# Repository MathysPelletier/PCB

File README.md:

Circuits imprimé pour la carte mère et le ESP32. Logiciel utilisé : KiCad 8.0

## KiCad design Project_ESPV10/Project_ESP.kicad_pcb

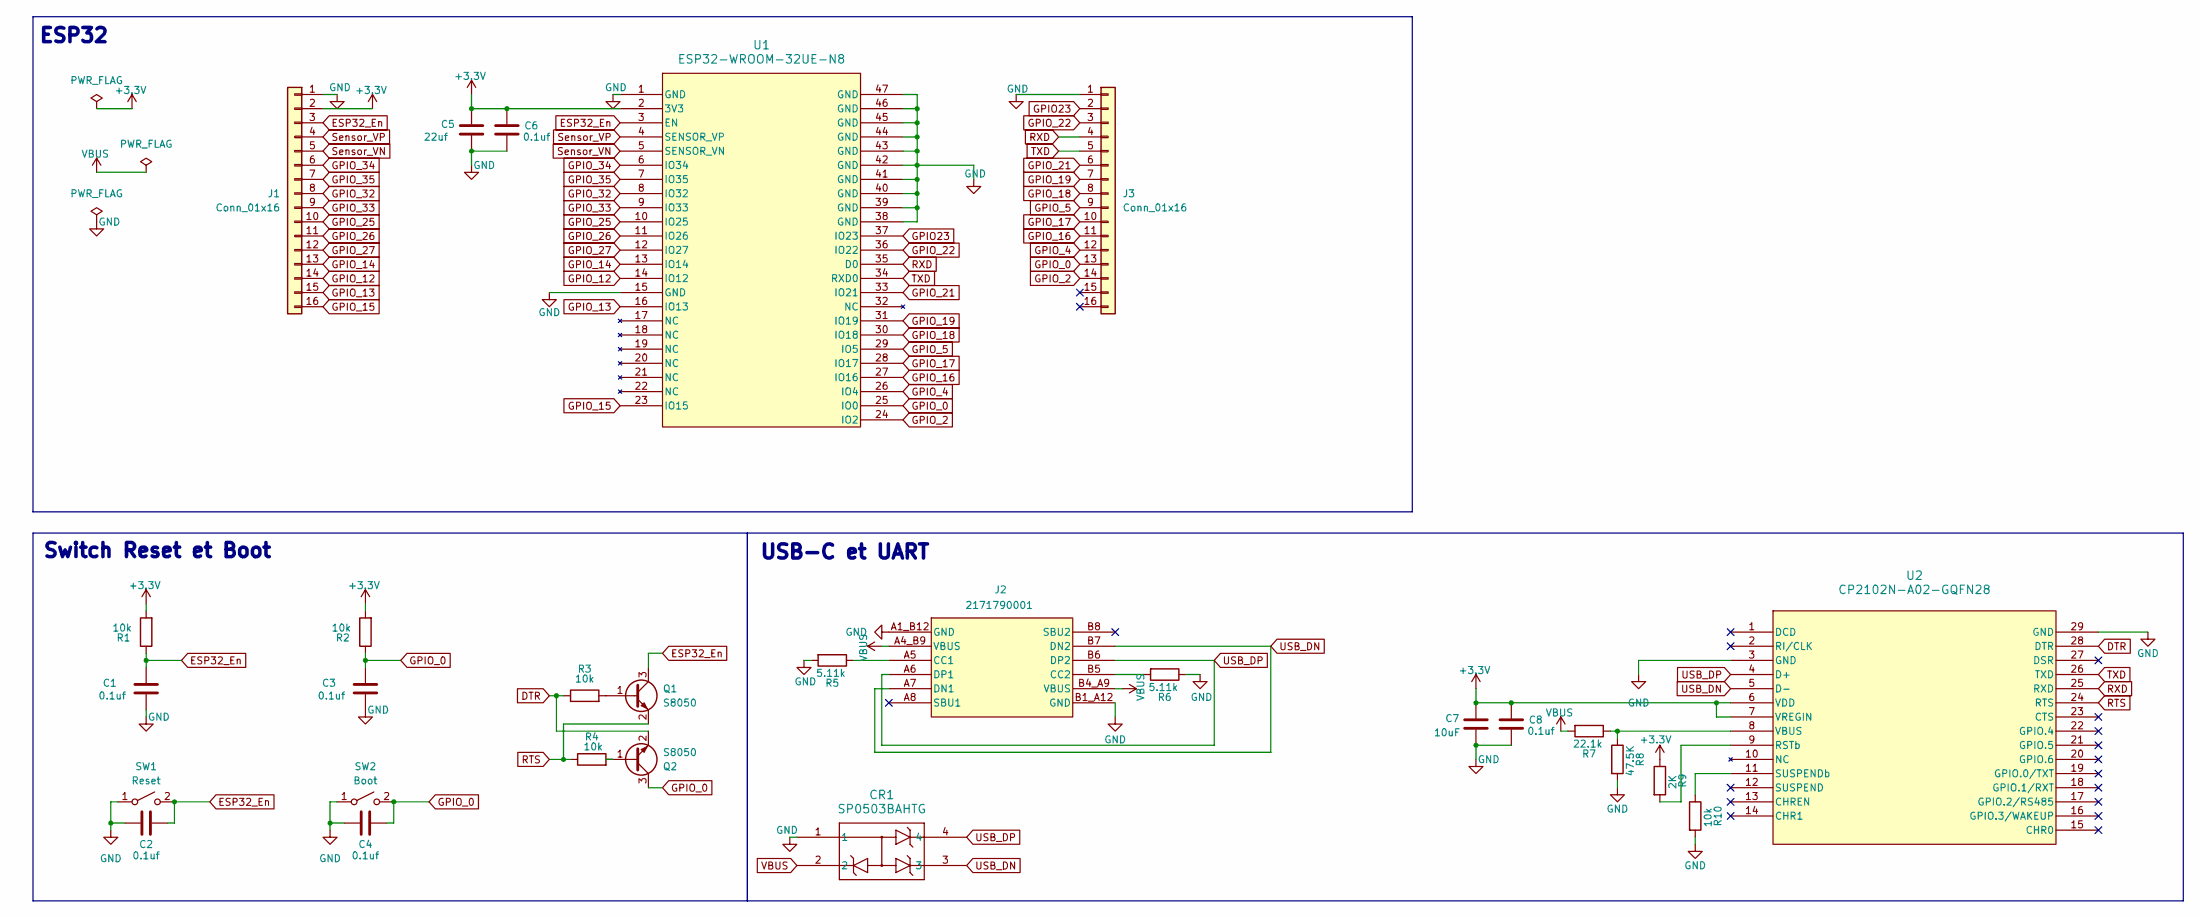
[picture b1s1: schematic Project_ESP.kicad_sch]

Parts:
C1, C2, C3, C4, C6, C8: 0.1uf; YAG_CC0603_YAG-M; part_number CC0603KRX7R8BB104
C5: 22uf; YAG_CC0603_YAG-M; part_number GRM188R61A226ME15D
C7: 10uF; YAG_CC0603_YAG-M; part_number JMK107ABJ106MA-T
CR1: SP0503BAHTG; TVS-SP05_LTF; part_number SP0503BAHTG
J1, J3: Conn_01x16; PinHeader_1x16_P2.54mm_Vertical
J2: 2171790001; GCT_USB4105-GF-A; PARTREV A1
Q1, Q2: S8050; TRAN_SS8050-G_CIP-M; part_number SS8050-G
R1, R2, R3, R4, R10: 10k; STA_RMCF0603_STP-M; part_number RMCF0603JT10K0
R5, R6: 5.11k; STA_RMCF0603_STP-M; part_number CRCW06035K11FKEAC
R7: 22.1k; STA_RMCF0603_STP-M; part_number RMCF0603FT22K1
R8: 47.5K; STA_RMCF0603_STP-M; part_number RMCF0603FT47K5
R9: 2K; STA_RMCF0603_STP-M; part_number ERJ-3EKF2001V
SW1: Reset; PTS636_SK; part_number PTS636 SK43 SMTR LFS
SW2: Boot; PTS636_SK; part_number PTS636 SK43 SMTR LFS
U1: ESP32-WROOM-32UE-N8; ESP32-WROOM-32UE_EXP; part_number ESP32-WROOM-32UE-N8
U2: CP2102N-A02-GQFN28; QFN28_5X5_SIL; part_number CP2102N-A02-GQFN28

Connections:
+3.3V: C5.2, C6.2, C7.2, C8.2, J1.2, R1.2, R2.2, R9.1, U1.2 (3V3), U2.6 (VDD), U2.7 (VREGIN)
DTR: Q2.2 (E), R3.1, U2.28 (DTR)
ESP32_En: C1.2, C2.2, J1.3, Q1.3 (C), R1.1, SW1.2 (B), U1.3 (EN)
GND: C1.1, C2.1, C3.1, C4.1, C5.1, C6.1, C7.1, C8.1, CR1.1, J1.1, J2.A1_B12 (GND), J2.B1_A12 (GND), J3.1, R5.2, R6.1, R8.2, R10.2, SW1.1 (A), SW2.1 (A), U1.1 (GND), U1.15 (GND), U1.38 (GND), U1.39 (GND), U1.40 (GND), U1.41 (GND), U1.42 (GND), U1.43 (GND), U1.44 (GND), U1.45 (GND), U1.46 (GND), U1.47 (GND), U2.3 (GND), U2.29 (GND)
GPIO23: J3.2, U1.37 (IO23)
GPIO_0: C3.2, C4.2, J3.13, Q2.3 (C), R2.1, SW2.2 (B), U1.25 (IO0)
GPIO_2: J3.14, U1.24 (IO2)
GPIO_4: J3.12, U1.26 (IO4)
GPIO_5: J3.9, U1.29 (IO5)
GPIO_12: J1.14, U1.14 (IO12)
GPIO_13: J1.15, U1.16 (IO13)
GPIO_14: J1.13, U1.13 (IO14)
GPIO_15: J1.16, U1.23 (IO15)
GPIO_16: J3.11, U1.27 (IO16)
GPIO_17: J3.10, U1.28 (IO17)
GPIO_18: J3.8, U1.30 (IO18)
GPIO_19: J3.7, U1.31 (IO19)
GPIO_21: J3.6, U1.33 (IO21)
GPIO_22: J3.3, U1.36 (IO22)
GPIO_25: J1.10, U1.10 (IO25)
GPIO_26: J1.11, U1.11 (IO26)
GPIO_27: J1.12, U1.12 (IO27)
GPIO_32: J1.8, U1.8 (IO32)
GPIO_33: J1.9, U1.9 (IO33)
GPIO_34: J1.6, U1.6 (IO34)
GPIO_35: J1.7, U1.7 (IO35)
unnamed: J2.A5 (CC1), R5.1
unnamed: J2.B5 (CC2), R6.2
unnamed: Q1.1 (B), R3.2
unnamed: Q2.1 (B), R4.2
unnamed: R9.2, U2.9 (RSTb)
unnamed: R10.1, U2.11 (SUSPENDb)
unnamed: R7.1, R8.1, U2.8 (VBUS)
RTS: Q1.2 (E), R4.1, U2.24 (RTS)
RXD: J3.4, U1.35 (D0), U2.25 (RXD)
Sensor_VN: J1.5, U1.5 (SENSOR_VN)
Sensor_VP: J1.4, U1.4 (SENSOR_VP)
TXD: J3.5, U1.34 (RXD0), U2.26 (TXD)
USB_DN: CR1.3, J2.A7 (DN1), J2.B7 (DN2), U2.5 (D-)
USB_DP: CR1.4, J2.A6 (DP1), J2.B6 (DP2), U2.4 (D+)
VBUS: CR1.2, J2.A4_B9 (VBUS), J2.B4_A9 (VBUS), R7.2

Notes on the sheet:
ESP32
Switch Reset et Boot
USB-C et UART

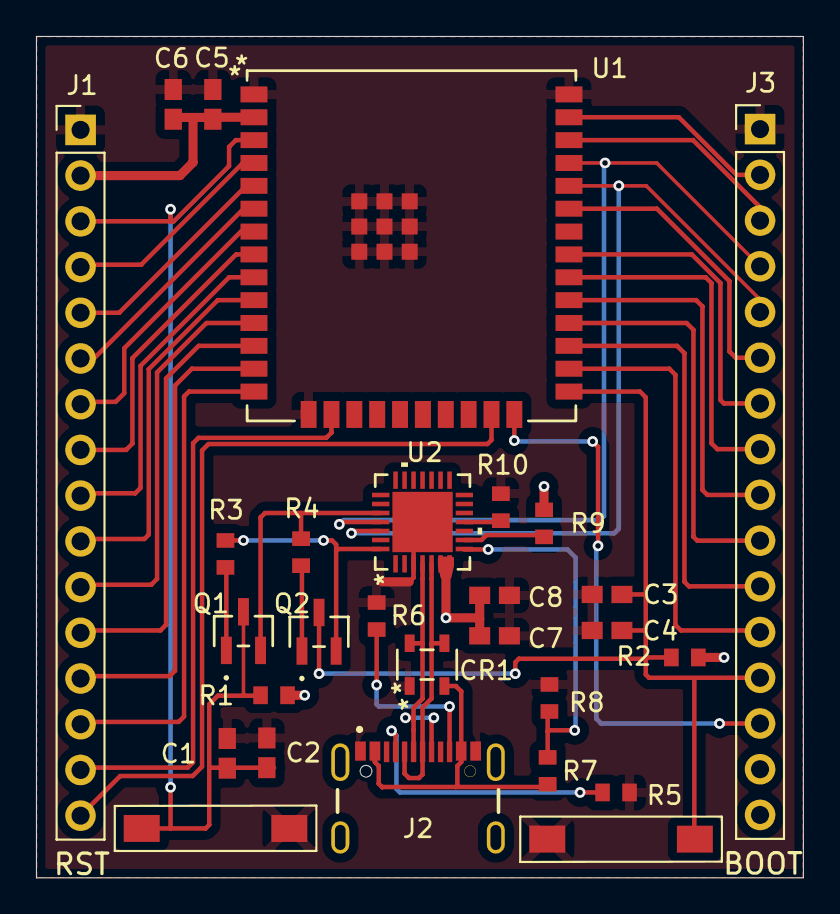
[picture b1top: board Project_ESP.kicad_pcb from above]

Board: 2 copper layers, 42.6 x 46.7 mm, 28 parts (0 on the bottom side), 41 nets.

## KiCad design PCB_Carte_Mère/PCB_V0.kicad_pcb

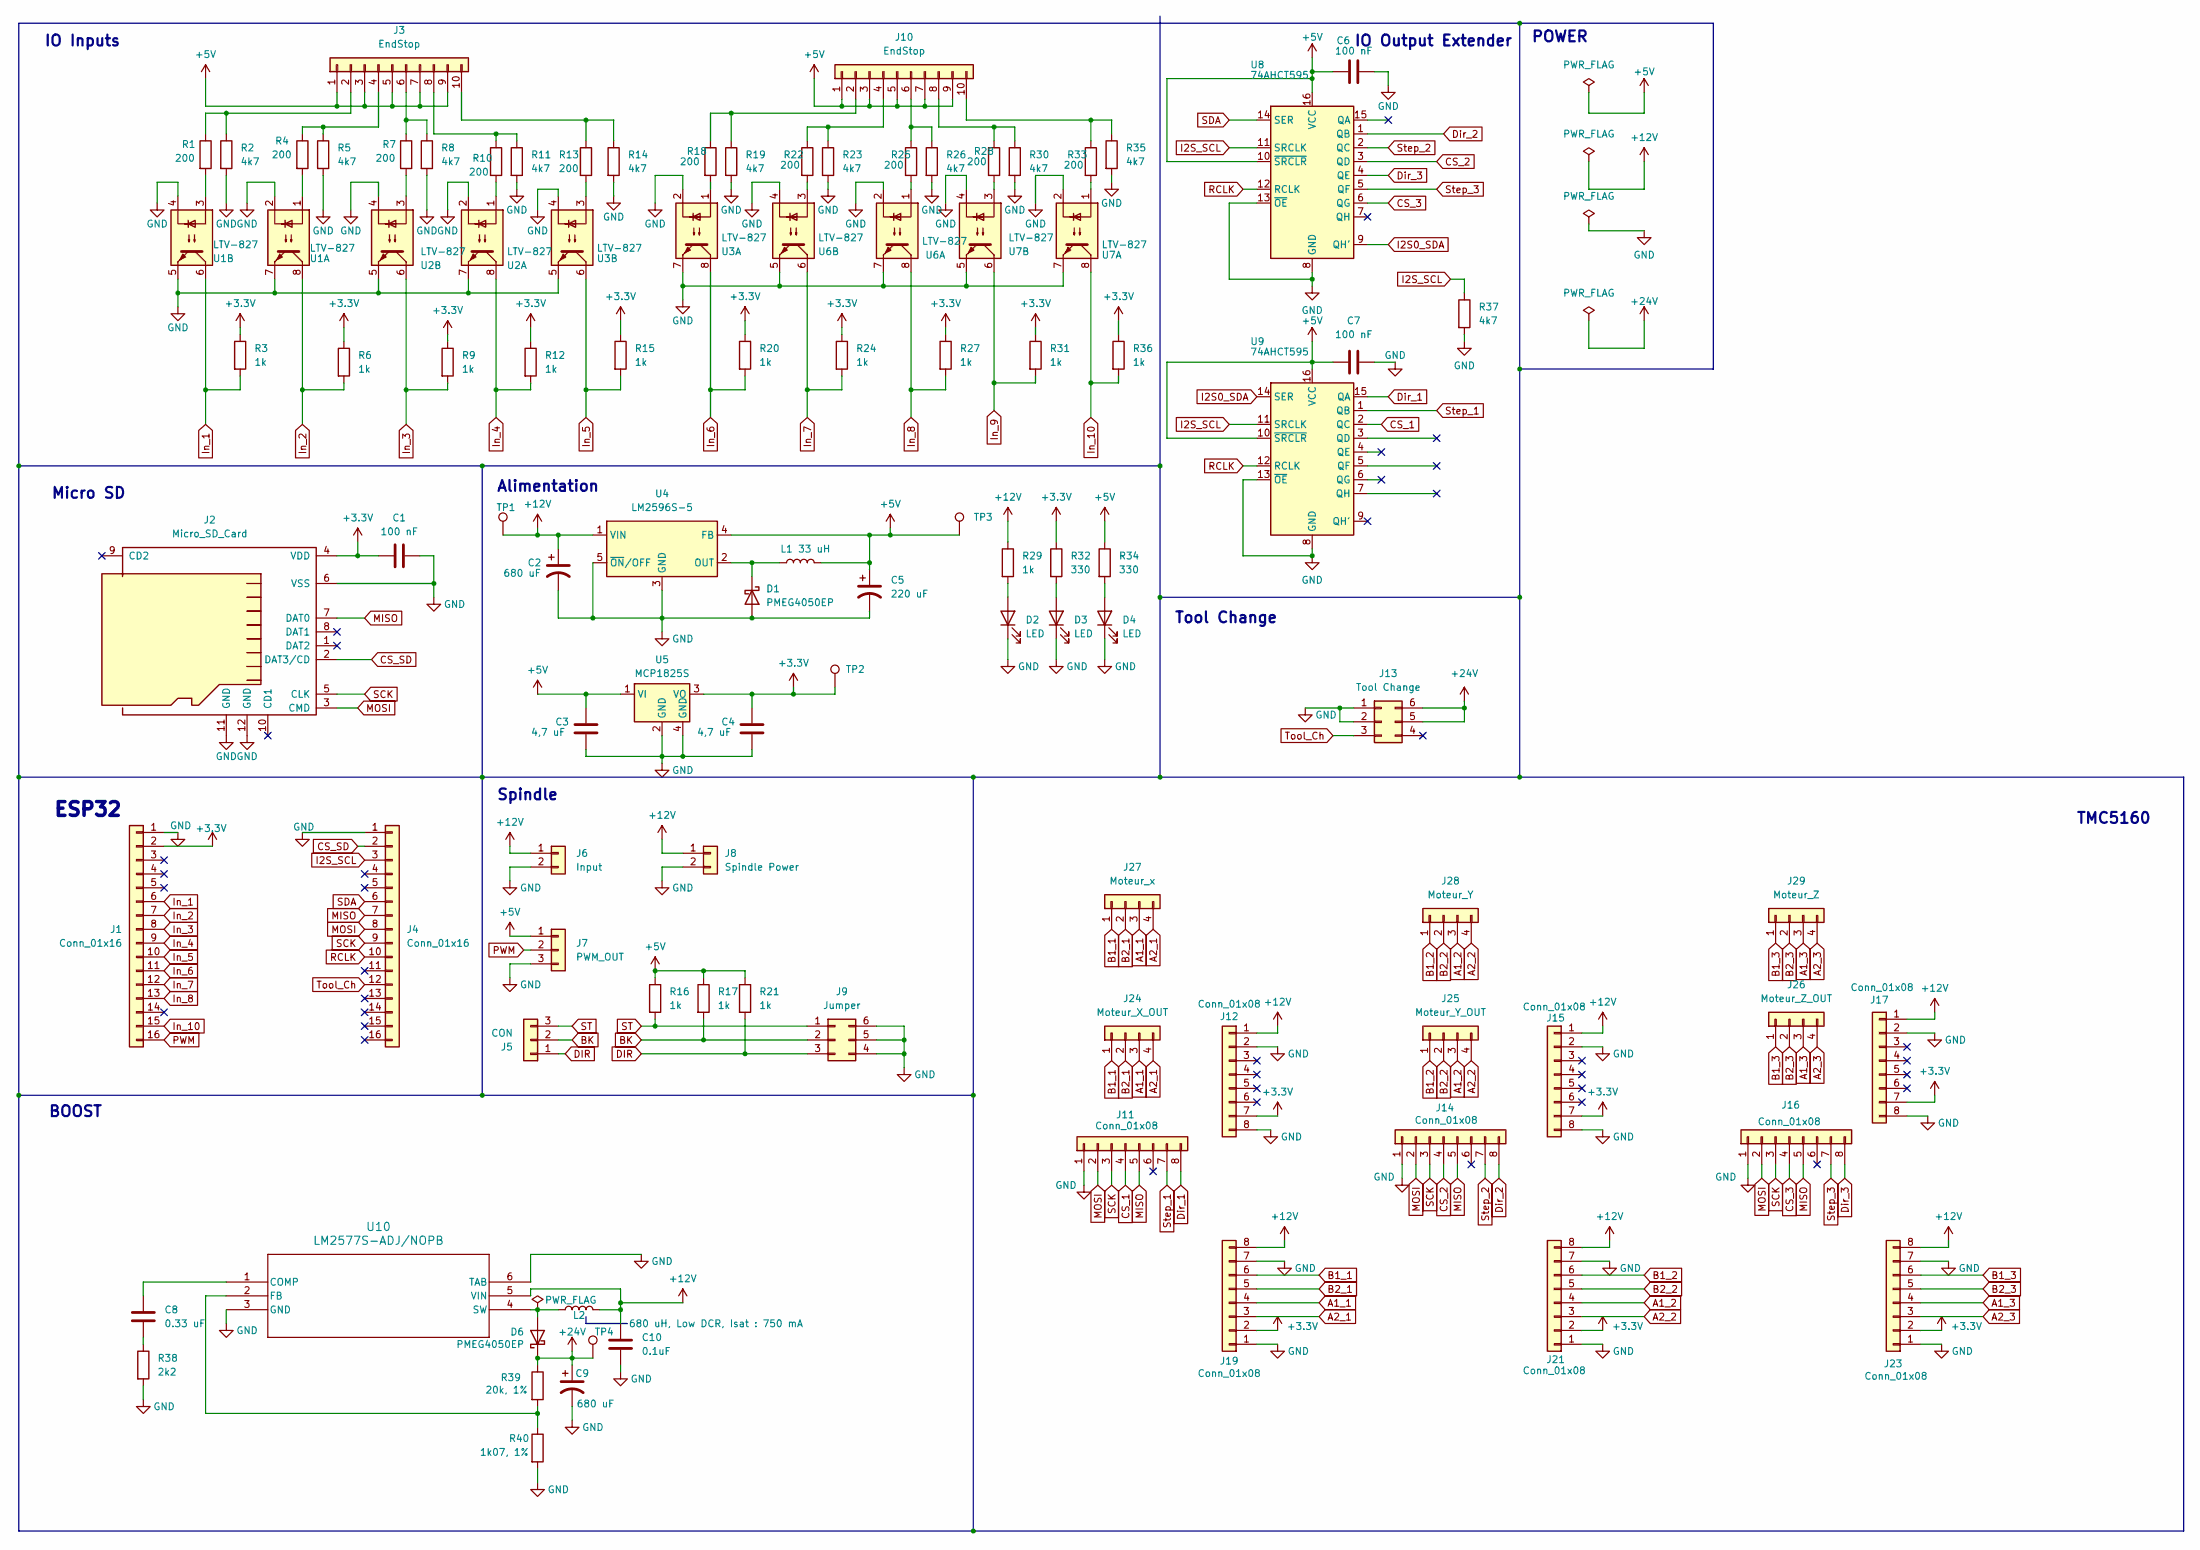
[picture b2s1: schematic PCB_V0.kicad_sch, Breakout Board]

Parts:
C1, C6, C7: 100 nF; C_0603_1608Metric
C2: 680 uF; Cap_680
C3, C4: 4,7 uF; C_0603_1608Metric
C5: 220 uF; Cap_220
C8: 0.33 uF; C_0603_1608Metric
C9: 680 uF; CAP_EKYC500_NIP
C10: 0.1uF; C_0603_1608Metric
D1, D6: PMEG4050EP; DIO_PMEG4050EP_115
D2, D3, D4: LED; D_0603_1608Metric
J1, J4: Conn_01x16; PinHeader_1x16_P2.54mm_Vertical
J2: Micro_SD_Card; GCT_MEM2061-01-188-00-A_REVA
J3, J10: EndStop; CONN10_1935242_PXC
J5: CON; CONN_1935174_PXC
J6: Input; CONN_1935161_PXC
J7: PWM_OUT; CONN_1935174_PXC
J8: Spindle Power; CONN_1935161_PXC
J9: Jumper; HARWIN_M20-9980346
J11, J12, J14, J15, J16, J17, J19, J21, J23: Conn_01x08; CONN_PPTC081LFBN-RC_SUL
J13: Tool Change; 61200621621
J24: Moteur_X_OUT; SULLINS_PPTC041LFBN-RC
J25: Moteur_Y_OUT; SULLINS_PPTC041LFBN-RC
J26: Moteur_Z_OUT; SULLINS_PPTC041LFBN-RC
J27: Moteur_x; 691137710004
J28: Moteur_Y; 691137710004
J29: Moteur_Z; 691137710004
L1: 33 uH; DR73
L2: 680 uH, Low DCR, Isat : 750 mA; IND_BOURNS_SRR1260
R1, R4, R7, R10, R13, R18, R22, R25, R28, R33: 200; R_0603_1608Metric
R2, R5, R8, R11, R14, R19, R23, R26, R30, R35, R37: 4k7; R_0603_1608Metric
R3, R6, R9, R12, R15, R16, R17, R20, R21, R24, R27, R31, R36: 1k; R_0603_1608Metric
R29: 1k; R_0805_2012Metric
R32, R34: 330; R_0603_1608Metric
R38: 2k2; R_0603_1608Metric
R39: 20k, 1%; R_0603_1608Metric
R40: 1k07, 1%; R_0603_1608Metric
TP1, TP2, TP3, TP4: TP420X150
U1, U2, U3, U6, U7: LTV-827; LVT-827S_LTO
U4: LM2596S-5; TO-263-5_TabPin3
U5: MCP1825S; SOT-223_3MC_MCH-M
U8, U9: 74AHCT595; SOP65P640X120-16N
U10: LM2577S-ADJ/NOPB; TS5B_TEX-M

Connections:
+3.3V: C1.2, C4.1, J1.2, J2.4 (VDD), J12.7, J15.7, J17.7, J19.2, J21.2, J23.2, R3.1, R6.1, R9.1, R12.1, R15.1, R20.1, R24.1, R27.1, R31.1, R32.1, R36.1, TP2.1, U5.3 (VO)
+5V: C3.1, C5.1, C6.1, C7.1, J3.1, J3.3, J3.5, J3.7, J3.9, J7.1, J10.1, J10.3, J10.5, J10.7, J10.9, L1.2, R16.1, R17.1, R21.1, R34.1, TP3.1, U4.4 (FB), U5.1 (VI), U8.10 (~SRCLR), U8.16 (VCC), U9.10 (~SRCLR), U9.16 (VCC)
+12V: C2.1, C10.1, J6.1, J8.1, J12.1, J15.1, J17.1, J19.8, J21.8, J23.8, L2.2, R29.1, TP1.1, U4.1 (VIN), U10.5 (VIN)
+24V: C9.1, D6.1 (K), J13.5, J13.6, R39.1, TP4.1
A1_1: J19.4, J24.3, J27.3
A1_2: J21.4, J25.3, J28.3
A1_3: J23.4, J26.3, J29.3
A2_1: J19.3, J24.4, J27.4
A2_2: J21.3, J25.4, J28.4
A2_3: J23.3, J26.4, J29.4
B1_1: J19.6, J24.1, J27.1
B1_2: J21.6, J25.1, J28.1
B1_3: J23.6, J26.1, J29.1
B2_1: J19.5, J24.2, J27.2
B2_2: J21.5, J25.2, J28.2
B2_3: J23.5, J26.2, J29.2
BK: J5.2, J9.2, R17.2
CS_1: J11.4, U9.2 (QC)
CS_2: J14.4, U8.3 (QD)
CS_3: J16.4, U8.6 (QG)
CS_SD: J2.2 (DAT3/CD), J4.2
DIR: J5.1, J9.3, R21.2
Dir_1: J11.8, U9.15 (QA)
Dir_2: J14.8, U8.1 (QB)
Dir_3: J16.8, U8.4 (QE)
GND: C1.1, C2.2, C3.2, C4.2, C5.2, C6.2, C7.2, C9.2, C10.2, D1.2 (A), D2.1 (K), D3.1 (K), D4.1 (K), J1.1, J2.6 (VSS), J2.11 (GND), J2.12 (GND), J4.1, J6.2, J7.3, J8.2, J9.4, J9.5, J9.6, J11.1, J12.2, J12.8, J13.1, J13.2, J14.1, J15.2, J15.8, J16.1, J17.2, J17.8, J19.1, J19.7, J21.1, J21.7, J23.1, J23.7, R2.2, R5.2, R8.2, R11.2, R14.2, R19.2, R23.2, R26.2, R30.2, R35.2, R37.2, R38.2, R40.2, U1.2, U1.4, U1.5, U1.7, U2.2, U2.4, U2.5, U2.7, U3.2, U3.4, U3.5, U3.7, U4.3 (GND), U4.5 (~ON/OFF), U5.2 (GND), U5.4 (GND), U6.2, U6.4, U6.5, U6.7, U7.2, U7.4, U7.5, U7.7, U8.8 (GND), U8.13 (~OE), U9.8 (GND), U9.13 (~OE), U10.3 (GND), U10.6 (TAB)
I2S0_SDA: U8.9 (QH'), U9.14 (SER)
I2S_SCL: J4.3, R37.1, U8.11 (SRCLK), U9.11 (SRCLK)
In_1: J1.6, R3.2, U1.6
In_2: J1.7, R6.2, U1.8
In_3: J1.8, R9.2, U2.6
In_4: J1.9, R12.2, U2.8
In_5: J1.10, R15.2, U3.6
In_6: J1.11, R20.2, U3.8
In_7: J1.12, R24.2, U6.6
In_8: J1.13, R27.2, U6.8
In_9: R31.2, U7.6
In_10: J1.15, R36.2, U7.8
MISO: J2.7 (DAT0), J4.7, J11.5, J14.5, J16.5
MOSI: J2.3 (CMD), J4.8, J11.2, J14.2, J16.2
unnamed: C8.2, R38.1
unnamed: D1.1 (K), L1.1, U4.2 (OUT)
unnamed: D2.2 (A), R29.2
unnamed: D3.2 (A), R32.2
unnamed: D4.2 (A), R34.2
unnamed: D6.2 (A), L2.1, U10.4 (SW)
unnamed: J3.2, R1.1, R2.1
unnamed: J3.4, R4.1, R5.1
unnamed: J3.6, R7.1, R8.1
unnamed: J3.8, R10.1, R11.1
unnamed: J3.10, R13.1, R14.1
unnamed: J10.2, R18.1, R19.1
unnamed: J10.4, R22.1, R23.1
unnamed: J10.6, R25.1, R26.1
unnamed: J10.8, R28.1, R30.1
unnamed: J10.10, R33.1, R35.1
unnamed: R1.2, U1.3
unnamed: R4.2, U1.1
unnamed: R7.2, U2.3
unnamed: R10.2, U2.1
unnamed: R13.2, U3.3
unnamed: R18.2, U3.1
unnamed: R22.2, U6.3
unnamed: R25.2, U6.1
unnamed: R28.2, U7.3
unnamed: R33.2, U7.1
unnamed: C8.1, U10.1 (COMP)
unnamed: R39.2, R40.1, U10.2 (FB)
PWM: J1.16, J7.2
RCLK: J4.10, U8.12 (RCLK), U9.12 (RCLK)
SCK: J2.5 (CLK), J4.9, J11.3, J14.3, J16.3
SDA: J4.6, U8.14 (SER)
ST: J5.3, J9.1, R16.2
Step_1: J11.7, U9.1 (QB)
Step_2: J14.7, U8.2 (QC)
Step_3: J16.7, U8.5 (QF)
Tool_Ch: J4.12, J13.3

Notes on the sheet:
TMC5160
POWER
Alimentation
IO Output Extender
Spindle
BOOST
IO Inputs
Micro SD
Tool Change
ESP32

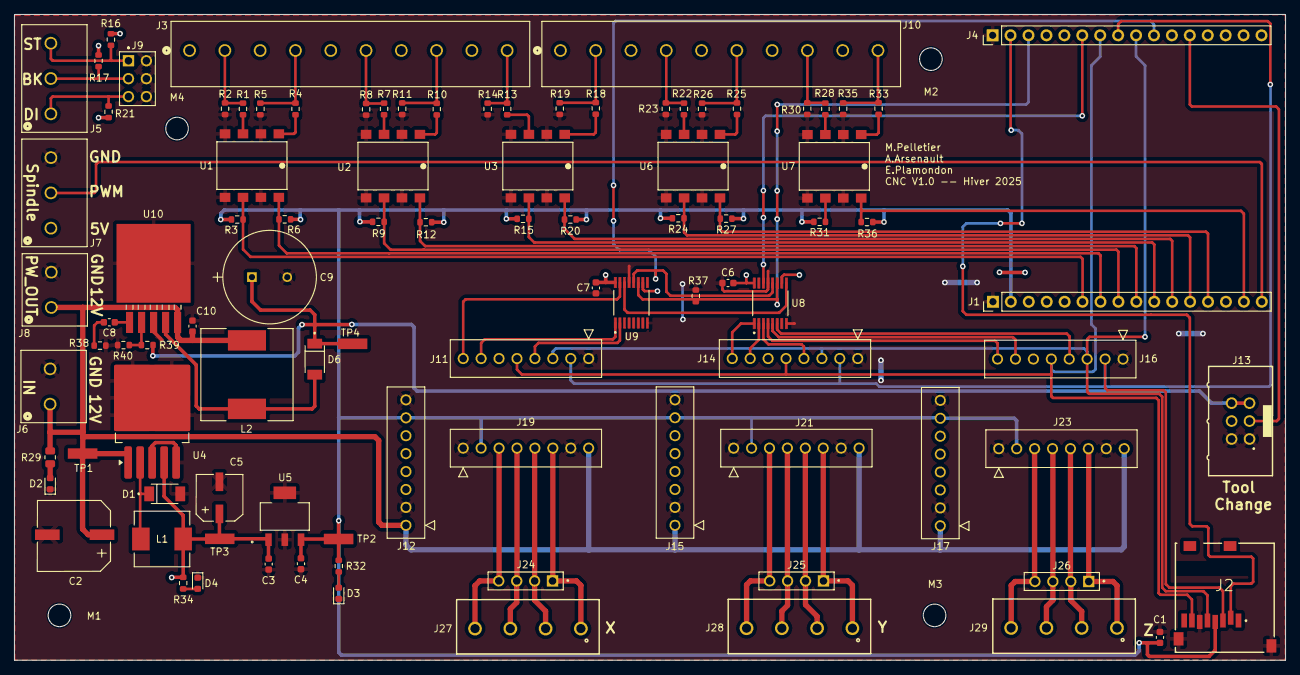
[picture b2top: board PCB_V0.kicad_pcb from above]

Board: 2 copper layers, 180.1 x 91.5 mm, 101 parts (0 on the bottom side), 77 nets.

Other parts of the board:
M1, M2, M3, M4: MountingHole_3.2mm_M3

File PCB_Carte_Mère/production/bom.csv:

Designator,Footprint,Quantity,Value,LCSC Part #
"C1, C6, C7",0603,3,100 nF,
C10,0603,1,0.1uF,
C2,Cap_680,1,680 uF,
"C3, C4",0603,2,"4,7 uF",
C5,Cap_220,1,220 uF,
C8,0603,1,0.33 uF,
C9,CAP_EKYC500_NIP,1,680 uF,
"D1, D6",DIO_PMEG4050EP_115,2,PMEG4050EP,
"D2, D3, D4",0603,3,LED,
"J1, J4",PinHeader_1x16_P2.54mm_Vertical,2,Conn_01x16,
"J10, J3",CONN10_1935242_PXC,2,EndStop,
"J11, J12, J14, J15, J16, J17, J19, J21, J23",CONN_PPTC081LFBN-RC_SUL,9,Conn_01x08,
J13,61200621621,1,Tool Change,
J2,GCT_MEM2061-01-188-00-A_REVA,1,Micro_SD_Card,
J24,SULLINS_PPTC041LFBN-RC,1,Moteur_X_OUT,
J25,SULLINS_PPTC041LFBN-RC,1,Moteur_Y_OUT,
J26,SULLINS_PPTC041LFBN-RC,1,Moteur_Z_OUT,
J27,691137710004,1,Moteur_x,
J28,691137710004,1,Moteur_Y,
J29,691137710004,1,Moteur_Z,
J5,CONN_1935174_PXC,1,CON,
J6,CONN_1935161_PXC,1,Input,
J7,CONN_1935174_PXC,1,PWM_OUT,
J8,CONN_1935161_PXC,1,Spindle Power,
J9,HARWIN_M20-9980346,1,Jumper,
L1,DR73,1,33 uH,
L2,IND_BOURNS_SRR1260,1,"680 uH, Low DCR, Isat : 750 mA",
"R1, R10, R13, R18, R22, R25, R28, R33, R4, R7",0603,10,200,
"R11, R14, R19, R2, R23, R26, R30, R35, R37, R5, R8",0603,11,4k7,
"R12, R15, R16, R17, R20, R21, R24, R27, R3, R31, R36, R6, R9",0603,13,1k,
R29,0805,1,1k,
"R32, R34",0603,2,330,
R38,0603,1,2k2,
R39,0603,1,"20k, 1%",
R40,0603,1,"1k07, 1%",
"TP1, TP2, TP3, TP4",TP420X150,4,~,
"U1, U2, U3, U6, U7",LVT-827S_LTO,5,LTV-827,
U10,TS5B_TEX-M,1,LM2577S-ADJ/NOPB,
U4,TO-263-5_TabPin3,1,LM2596S-5,
U5,SOT-223_3MC_MCH-M,1,MCP1825S,
"U8, U9",SOP65P640X120-16N,2,74AHCT595,

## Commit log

2025-05-15 Ajout du Projet PCB pour la carte mère
2025-05-15 Ajout du PCB ESP32
2025-05-19 Ajout du PDF carte mère
